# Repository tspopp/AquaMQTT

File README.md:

# AquaMQTT

AquaMQTT is a project designed to monitor and control your DHW heat pump locally using MQTT.

## Features

- Access sensor data and operational states from your heat pump.
- Control the heat pump: Set operational states e.g. water temperature and operation modes.
- [Automate the behavior of your heat pump according to your local energy production or energy availability](/README-PV.md)
- Easily integrate AquaMQTT with smart home systems like [Home Assistant](https://www.home-assistant.io/).

## Compatible Devices

AquaMQTT has been designed and tested with the [Windhager AquaWin Air3](https://www.windhager.com/en/products/hot-water-tanks/aquawin-air3/) DHW heat pump. While specifically tailored to this model, it has been proofen that AquaMQTT is compatible to similar heat pumps manufactured by the [Groupe Atlantic](https://www.groupe-atlantic.fr/) and branded for various companies such as:

- [Atlantic Explorer](https://www.atlantic-comfort.com/Water-Heaters/Heat-pump-water-heaters/Explorer)
- [Atlantic Calypso](https://atlantic-comfort.com/products/domestic-hot-water/heat-pump-water-heaters/calypso-vm)
- [Austria Email Explorer](https://www.austria-email.de/produkte/waermepumpensysteme/waermepumpen-trinkwasser/explorer-evo-2/)
- [Panasonic DHW270](https://www.aircon.panasonic.eu/CH_de/model/paw-dhw270f/)
- [Sauter Confort Pagosa Green](https://www.confort-sauter.com/chauffe-eau/pagosa-green)
- [Thermor Aeromax](https://www.thermor.com/our-solutions/renewable-energy-solutions/heat-pump-water-heaters/aeromax-premium)

A list of community proofen compatible devices is [here](./DEVICES.md).

## How does it work?

AquaMQTT facilitates communication between the HMI controller and the main controller of your heat pump. The project intercepts the serial messages exchanged between these controllers, extracts and parses identified values, and publishes them via [MQTT](./MQTT.md). For a detailed description of the heat pump's serial protocol, refer to [PROTOCOL.md](./PROTOCOL.md).

To achieve this communication interception, an Arduino-based microcontroller is introduced between the communication lines of the HMI controller and the main controller.

AquaMQTT not only monitors the heat pump's status but also provides the capability to control it by modifying the messages originating from the HMI controller. This allows you to set operational states, such as water temperature and operation modes, directly through AquaMQTT.

## Getting Started

- [Hardware Requirements](/pcb) 

- [Software Installation](AquaMQTT/README.md)

- [Heatpump Modification](./WIRING.md)

## Why not using cozytouch / io-homecontrol?

Unfortunately, I had no success pairing those solutions with my Windhager branded heatpump. Moreover, this solution is independent from any manufacturer backends and therefore running entirely within your private local area network. 

## Further Reading

- [HomeAssistant Integration](./HOMEASSISTANT.md)

- [Troubleshooting / F.A.Q](./TROUBLESHOOTING.md)

- [Compatible Devices](./DEVICES.md)
 
- [Heat pump serial protocol (LEGACY)](./PROTOCOL.md)

- [Heat pump serial protocol (NEXT)](./PROTOCOL_NEXT.md)

- [Heat pump serial protocol (ODYSSEE)](./PROTOCOL_ODYSSEE.md)

- [Available MQTT Topics and Payloads](./MQTT.md)

- [Utilize excess local energy using PV modes](./README-PV.md)

## References

- 🇫🇷 https://forum.hacf.fr/t/integration-dun-chauffe-eau-atlantic-explorer-en-mqtt/40493/6
- 🇳🇱 https://gathering.tweakers.net/forum/list_messages/2116816/78
- 🇩🇪 https://forum.iobroker.net/topic/61801/skript-atlantic-w%C3%A4rmepumpe-%C3%BCber-cozytouch-abfragen/74

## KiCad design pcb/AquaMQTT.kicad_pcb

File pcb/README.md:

# AquaMqtt PCB Board

The AquaMQTT PCB Board is intended to be installed between the communication wires of the DHW HMI Controller and the DHW
Mainboard. To enable the communication to both HMI Controller and DHW Mainboard, the board provides two
individual [USART entities in One-Wire Mode](https://ww1.microchip.com/downloads/en/AppNotes/USART-in-One-Wire-Mode-ApplicationNote-DS00002658.pdf).
The Arduino ESP32 on the board runs AquaMQTT, providing communication via WiFi/MQTT while being powerful enough to
handle any time critical USART communication with the heat pumps hmi controller and main board.

The boards are designed using [Kicad](https://www.kicad.org/). If you want to edit the layout, you may need to install an
additional [Arduino Kicad library](https://github.com/Alarm-Siren/arduino-kicad-library) before opening/editing the
project.

## Changelog

| Version | Description                                       |
|---------|---------------------------------------------------|
| 2.0     | RAST Sockets, SMD SN74LVC2T45, Pre-assembly Ready |
| 1.0     | Initial Design, Self-Soldering                    |

## Revision 2.0

***Note*: Revision 2.0 needs AquaMQTT v1.7.0 or later for MITM mode**

This revision fixes an issue, where [certain heatpumps](https://github.com/tspopp/AquaMQTT/issues/67) were not able to communicate due to a very sensitive serial link and changes of impedance. The Logic-Level-Converter and the one-wire USART circuit have been replaced by two [SN74LVC2T45](https://www.ti.com/lit/ds/symlink/sn74lvc2t45.pdf?ts=1740403453841&ref_url=https%253A%252F%252Fwww.ti.com%252Fproduct%252Fde-de%252FSN74LVC2T45). Thanks to [@Arrnooo](https://github.com/Arrnooo) for debugging, verifying and providing a new design proposal.

Additionally, this revision adds optional RAST sockets. Thanks to [@tukutt](https://github.com/tukutt) for providing the design and custom adapters, originally used with revision 1.0 of the AquaMQTT board (see below).

### Buy Pre-Assembled

This board uses tiny SMD SSOP parts (SN74LVC2T45) so self-soldering is most probably an issue. This revision is meant to be bought pre-assembled from [JLCPCB](https://jlcpcb.com/)

1. Upload `AquaMQTT_Board_Revision_v2.zip` as *gerber file*
2. Enable "PCB Assembly"
3. Proceed and upload `AquaMQTT_Board_Revision_v2_BOM.csv` as *BOM*
4. Proceed and upload `AquaMQTT_Board_Revision_v2_CPL.csv` as *CPL*
5. Verify matched parts (should be good out of the box)
6. Verify component placement (should be good out of the box)

If there are any issues during production, [you may reference a successful previous order](https://github.com/tspopp/AquaMQTT/issues/96).

### Parts

| Item                                                                                                                                                                                     | Count | Estimated Cost |
|------------------------------------------------------------------------------------------------------------------------------------------------------------------------------------------|-------|----------------|
| Pre-Soldered AquaMQTT Board (Revision 2.0)  (https://jlcpcb.com/)                                                                                                                        | 1x    | ~ 6 $          |
| [Arduino Nano ESP32](https://docs.arduino.cc/hardware/nano-esp32) with Headers (ABX00083). Note: Community suggested [cheaper alternative](https://github.com/tspopp/AquaMQTT/issues/56) | 1x    | ~ 5-20 €       |

## Revision 1.0

**First revision, which is still good to use. There is no need to replace it with revision 2.0 in case it works for your heatpump.**

An optional DS3231 Real Time Clock might be added to the board. This might be handy in case AquaMQTT will be ever used without any HMI at all. It would ensure a recovery with correct date and time after power outage and without WiFi.
**Adding a RTC Module is experimental and untested!**

### RAST vs. 2x4 Connector

Your [heat pump](./../DEVICES.md) may use a different connector such as the Thermor Aeromax 5. Happily [@tukutt](https://github.com/tukutt) designed an [adapter pcb](https://oshwlab.com/tukutt/aquamqtt-original-pcb-to-rast-co) to connect those heatpumps without cutting any cables. Read more about this in [#51](https://github.com/tspopp/AquaMQTT/issues/51).

### BOM

| Item                                                                                                                                                             | Count | Estimated Cost |
|------------------------------------------------------------------------------------------------------------------------------------------------------------------|-------|----------------|
| AquaMqtt PCB Board (e.g. via AISLER.net)                                                                                                                         | 1x    | ~ 7 €          |
| [Arduino Nano ESP32](https://docs.arduino.cc/hardware/nano-esp32). Note: Community suggested [cheaper alternative](https://github.com/tspopp/AquaMQTT/issues/56) | 1x    | ~ 20 €         |
| Cable 2x4 2,54mm (Socket-Housing, Contacts, Wiring, [Dupont](https://amzn.eu/d/fQyKTWX)                                                                          | 1x    | ~ 10 €         |
| [Real Time Clock RTC DS3231](https://www.az-delivery.de/products/ds3231-real-time-clock) *(optional, experimental)*                                              | (1x)  | ~ 6 €          |
| [SparkFun Logic Level Converter](https://eckstein-shop.de/SparkFunLogicLevelConverter-Bi-DirectionaShifterPegelwandlerEN) - 3.3V to 5V Bi-Directional or similar | 1x    | ~ 4 €          |
| 100k Resistance 0207 (Ø x L) 2.5 mm x 6.8 mm                                                                                                                     | 3x    | < 1 €          |
| 10k Resistance 0207 (Ø x L) 2.5 mm x 6.8 mm                                                                                                                      | 3x    | < 1 €          |
| 4.7k Resistance 0207 (Ø x L) 2.5 mm x 6.8 mm                                                                                                                     | 3x    | < 1 €          |
| [Transistor BC547A TO-92](https://www.conrad.de/de/p/tru-components-transistor-bjt-diskret-tc-bc547a-to-92-anzahl-kanaele-1-npn-1581825.html)                    | 4x    | < 1 €          |
| Pin Header 2x4 2,54mm                                                                                                                                            | 2x    | < 1 €          |
| [Pin Header 1x4 2,54mm](https://www.conrad.de/de/p/mpe-garry-stiftleiste-standard-anzahl-reihen-1-polzahl-je-reihe-4-087-1-004-0-s-xs0-1260-1-st-733940.html)    | 2x    | < 1 €          |
| [Pin Header 1x2 2,54mm](https://www.conrad.de/de/p/mpe-garry-stiftleiste-standard-anzahl-reihen-1-polzahl-je-reihe-2-087-1-002-0-s-xs0-1260-1-st-733900.html)    | 1x    | < 1 €          |

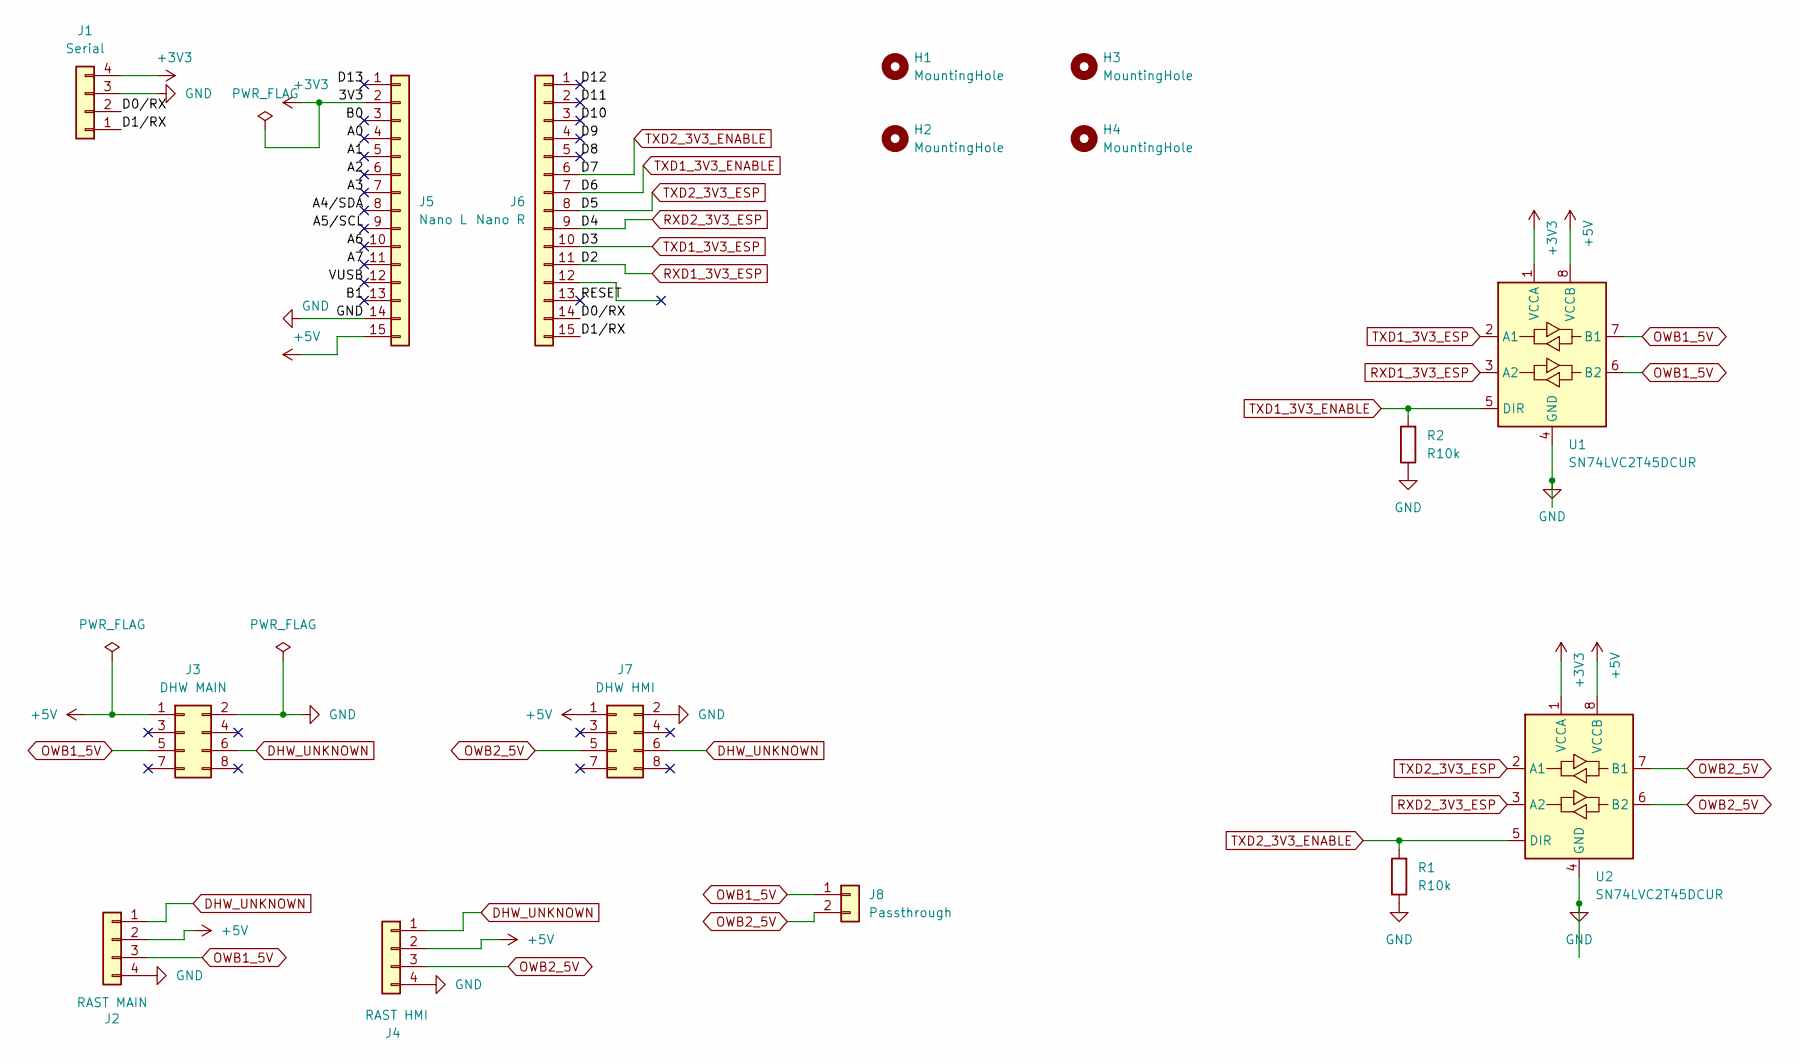
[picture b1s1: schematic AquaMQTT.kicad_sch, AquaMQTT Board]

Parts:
H1, H2, H3, H4: MountingHole; MountingHole_4.3mm_M4_DIN965
J1: Serial; PinHeader_1x04_P2.54mm_Vertical; LCSC C5116483
J2: RAST MAIN; RAST_3517-06_(2.5MM)_2 COPY
J3: DHW MAIN; PinHeader_2x04_P2.54mm_Vertical; LCSC C32713277
J4: RAST HMI; RAST_3517-06_(2.5MM)_2 COPY
J5: Nano L; PinSocket_1x15_P2.54mm_Vertical; LCSC C7499333
J6: Nano R; PinSocket_1x15_P2.54mm_Vertical; LCSC C7499333
J7: DHW HMI; PinHeader_2x04_P2.54mm_Vertical; LCSC C32713277
J8: Passthrough; PinHeader_1x02_P2.54mm_Vertical; LCSC C5360898
R1, R2: R10k; R_Axial_DIN0207_L6.3mm_D2.5mm_P10.16mm_Horizontal; LCSC C410695
U1, U2: SN74LVC2T45DCUR; SSOP-8_2.95x2.8mm_P0.65mm; LCSC C347590

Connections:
+3V3: J1.4, J5.2, U1.1 (VCCA), U2.1 (VCCA)
+5V: J2.2, J3.1, J4.2, J5.15, J7.1, U1.8 (VCCB), U2.8 (VCCB)
/A0: J5.4
/A1: J5.5
/A2: J5.6
/A3: J5.7
/A4/SDA: J5.8
/A5/SCL: J5.9
/A6: J5.10
/A7: J5.11
/B0: J5.3
/B1: J5.13
/D0/RX: J1.2, J6.14
/D1/RX: J1.1, J6.15
/D8: J6.5
/D9: J6.4
/D10: J6.3
/D11: J6.2
/D12: J6.1
/D13: J5.1
/RESET: J6.13
/VUSB: J5.12
DHW_UNKNOWN: J2.1, J3.6, J4.1, J7.6
GND: J1.3, J2.4, J3.2, J4.4, J5.14, J7.2, R1.1, R2.1, U1.4 (GND), U2.4 (GND)
OWB1_5V: J2.3, J3.5, J8.1, U1.6 (B2), U1.7 (B1)
OWB2_5V: J4.3, J7.5, J8.2, U2.6 (B2), U2.7 (B1)
RXD1_3V3_ESP: J6.11, U1.3 (A2)
RXD2_3V3_ESP: J6.9, U2.3 (A2)
TXD1_3V3_ENABLE: J6.7, R2.2, U1.5 (DIR)
TXD1_3V3_ESP: J6.10, U1.2 (A1)
TXD2_3V3_ENABLE: J6.6, R1.2, U2.5 (DIR)
TXD2_3V3_ESP: J6.8, U2.2 (A1)

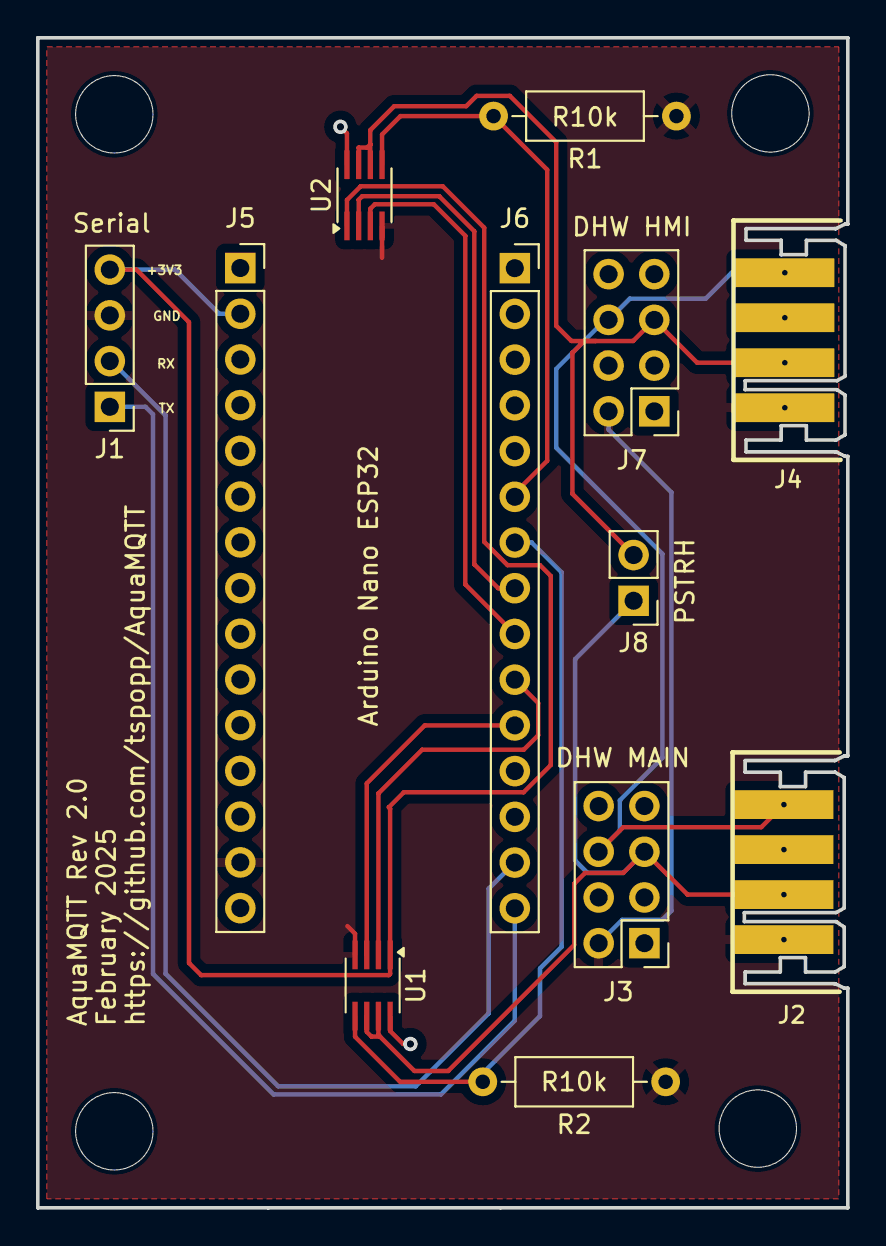
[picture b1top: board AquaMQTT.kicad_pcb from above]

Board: 2 copper layers, 45.0 x 65.0 mm, 16 parts (0 on the bottom side), 14 nets.

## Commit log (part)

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2023-09-08 init(media)
2023-09-08 init(repo): protocol and basic mqtt bridge
2023-09-09 feat(logger): provide operation mode and type
2023-09-10 feat(logger): provide heatpump states
2023-09-10 update(screenshot): homeassistant
2023-09-10 feat(logger): provide heatpump states (#2)
2023-09-10 fix(workflow): working directory
2023-09-10 feat(workflow): add github workflow for platformio build (#3)
2023-11-06 draft(control): building hmi messages, control heatpump
2023-11-06 draft(simulation): simple uno sketch which simulates the main heatpump controller
2023-11-06 doc(Hardware): added section regarding hardware
2023-11-07 feat(prototype): proof controlability of heatpump (#4)
    Added simple sketch which simulates the main controller.
    Added functionality to control the heatpump to AquaMQTTLogger.
    Updated Documentation and Roadmap
    Proof of communication to hmi controller and main controller.
2023-11-13 add(board): added pcb board images
2023-11-13 feat(pcb): initial pcb layout
2023-12-07 docs(README): updated roadmap
2023-12-09 fix(warnings): clang etc..
2023-12-09 init(aquamqtt): basic functionality
2023-12-09 refactor(aquamqtt): various improvements
2023-12-09 doc(readme): updated readme
2023-12-09 refactor(constants): get rid of magic numbers
2023-12-09 feat(mqtt-controlability): prepare more hmi overrides
2023-12-09 fix(reset): reduced ntp timeout which lead to watchdog reset
2023-12-09 refactor(mqtt): refactored mqtt messages
2023-12-09 doc(readme): more nicer readme
2023-12-09 doc(readme): more readme
2023-12-09 fix(build): 2
2023-12-09 feat(aquamqtt): initial version
2023-12-11 fix(temp, installationConfig, watchdog): fixes various issues
2023-12-11 fix(mqtt): fixed mqtt update frequency
2023-12-20 fix(aquamqtt): fixed various issues observed during the initial trial
    Added MQTT Command reset to remove all overrides in MITM mode at once
    Added MQTT Topic activeOverrides which provides a status on all overrriden values in MITM mode
    Fixed Parsing of DHW's Installation Mode
    Fixed Parsing of Float Temperatures (Negative Values e.g. -0.1°C were broken)
    Fixed OTA and Unexpected Reboots due to Watchdog: Increased Watchdog Timer to 60 seconds
    Fixed MQTT Update Cycle: MQTT Topics are now only updated, when a change in the DHW message occur
2023-12-20 doc(wiring): init
2023-12-23 fix(time): fixed invalid date and time values in override mode
2024-01-09 docs(wiring): use media
2024-01-09 fix(suffix): fixed file suffix
2024-01-09 doc(readme): updated images
2024-01-29 fix(connectivity): reconnect to mqtt on lost connection (#10)
2024-02-12 fix(connectivity): proper wifi reconnect
2024-02-23 feat(pv-overrides): use excess energy to reach maximum temperature
2024-02-23 revert(customconfig)
2024-02-23 fix(link)
2024-02-27 feat(pv-overrides): use excess energy to reach maximum temperature (#11)
2024-04-20 doc(mqtt): fix typo in pv heatelement topic
2024-04-20 doc(mqtt): fix typo in pv heatelement topic (#13)
2024-04-23 Add Home Assistant Configuration for AquaMQTT
    English version.
    Change "atlantic_" with your device name.
    Adapt "state_topic:" with your path
2024-04-24 feat(homeassistant): add example homeassistant configuration (#15)
    Add Home Assistant Configuration for AquaMQTT:
    English version.
    Change "atlantic_" with your device name.
    Adapt "state_topic:" with your path
    Thanks to @scoudibou!
2024-05-01 doc(readme): add potential device from sauter confort
2024-05-16 doc(readme): added thermor airomax 5 as proofen device
2024-05-28 doc(mqtt): update mqtt topics
2024-05-28 feat(mitm): transfer errors in mitm mode
2024-05-28 feat(debug): option to publish raw messages
2024-05-28 fix(fan): represent fan speed in percent not rpm
2024-05-28 feat(parsing): parse pv input status and states
2024-05-28 feat(protocol): documented latest protocol findings
2024-05-28 feat(parsing): implemented settings provided from main
2024-05-28 fix(mitm): fixed dropped bytes in main channel
2024-05-28 chore(doc): update latest protocol findings
2024-06-12 doc(readme): added austria email explorer evo 2 as proofen device
2024-06-12 feat(pv-overrides): show solar and pv icons on hmi controller
2024-06-15 refactor(progmem): use constexpr instead of progmem
2024-06-15 revert(ota)
2024-06-15 feat(aquadbg): another troubleshooting tool
2024-06-15 refactor(progmem)
2024-06-15 doc(troubleshooting): add section regarding AquaDebug
2024-06-15 feat(aquadbg): more troubleshooting tooling (#27)
2024-08-17 adapted documentation to new attribute
2024-08-17 revert platformio ota
2024-08-19 chore(renaming): renamed from water consumption to production
2024-08-19 homeassistant
2024-08-19 fix(wifi): do not trust platform auto reconnect routines (#32)
2024-09-11 refactor(framebuffer): remove dead code left from debugging session
    - fixes #34
2024-09-13 feat(framework): upgrade to arduino core 3.0.4 / esp-idf v5.1.4 via pioarduino
    - fixes #35
2024-09-14 revert(framework): back to v4 framework due to broken ota and ntp
2024-10-13 feat(filter): filter temperature values published to mqtt using kalman filter
2024-10-13 fix(aquamqtt): fix broken ntp update
2024-10-14 feat(mqtt): filter temperature values using kalman (#38)
2024-10-19 chore(various): enable unittests in ci, pin library versions, adapt watchdog, remove magic numbers
2024-10-20 feat(homeassistant): enable homeassistant discovery
    refactor(mqtt): use arduino json for overrides
    doc(homeassistant): some remarks to homeassistant integration
    refactor(discovery): various items from test
2024-10-24 feat(fan): allow controlability of airduct and exhaust fan configuration
2024-10-24 chore(version): increase version
2024-10-24 feat(fan): allow controlability of airduct and exhaust fan configuration (#44)
2024-10-29 Add water_heater integration
    https://www.home-assistant.io/integrations/water_heater.mqtt/
2024-11-01 feat(mqtt): more options to disable frequent changing topics
2024-11-01 feat(homeassisant): add water heater integration to auto discovery
2024-11-02 Add .vscode folder to gitignore
2024-11-02 Added option for uploading with Esptool in Platformio
2024-11-03 chore(homeassistant): add water_heater to homeassistant template
2024-11-03 chore(homeassistant): add water_heater to homeassistant template
    * Add water_heater integration
    https://www.home-assistant.io/integrations/water_heater.mqtt/
    * chore(homeassistant): add water_heater to homeassistant template
    ---------
2024-11-03 feat(mqtt): configuration options to disable several debugging mqtt topics (#48)
    * feat(mqtt): more options to disable frequent changing topics
    * config: set serial statistics to on by default
2024-11-03 wip(protocol-next): first steps
2024-11-04 wip(protocol): doc, fixed date, add water temp target, add operation type and modes
2024-11-05 wip(protocol): pv status
2024-11-09 wip(protocol): prepare to support both protocols in parallel
2024-11-09 wip(protocol): parse timers
2024-11-09 wip(protocol): power heatpump, total energy, total energy heatpump
2024-11-10 doc(devices): rast adapter, list of devices with sw version
2024-11-11 doc(devices): rast adapter, list of devices with sw version (#54)
2024-11-11 wip(protocol): identified error messages
2024-11-12 wip(protocol): proper checksum calcuation and generation, parse errors, enable mitm (experimental)
2024-11-15 Update PROTOCOL_NEXT.md
    Texts corrected
    To-dos completed
    Unassigned values added
2024-11-20 refactor(protocols): support multiple protocols
2024-11-20 wip(protocol): main states, pwm fan speed
2024-11-25 fix(build): disable custom configuration for pipeline to success
2024-11-25 hack(watchdog): intermediate fix for reboot issue
2024-11-26 experimental(next): allow overrides in mitm mode
2024-11-26 doc(mqtt): fix table
2024-11-26 feat(protocol-next): initial support for additional heatpump protocol E/E
2024-12-04 feat(protocol-next): full support of E/E protocol (next)
2025-01-19 Update framework and wifi handler
2025-01-19 feat(aquadebug): build aquadebug in ci/cd, pin versions
2025-01-19 feat(aquadebug): build aquadebug in ci/cd, pin versions (#61)
2025-01-19 feat(platformio): add environment for esp32-s3-devkitc-1
2025-01-19 feat(platformio): add environment for esp32-s3-devkitc-1 (#62)
2025-01-19 feat(aquamqtt): support legacy protocol with XOR checksum
2025-01-19 build(esp32-devkit): apply suggestions from community
2025-02-03 add tx enable gpio for hmi and controller channel
2025-02-10 prepare(protocol-odyssee): preparation for another heat-pump protocol
2025-02-11 Update configuration to reduce amount of MQTT messages by default
    This resolves issues with specificly new users that are getting unexpected results due to a flood of update messages.
2025-02-11 chore(mqtt): disable debug and time/date topics in default configuration
    This resolves issues with specificly new users that are getting unexpected results due to a flood of update messages.
2025-02-11 doc(mqtt): add note how to enable serial debug options
2025-02-14 wip(odyssee): parse operation mode accordingly
2025-02-15 fix(odyssee): provide time and date
2025-02-15 feat(odyssee): add totalPower and grid voltage from message 217
2025-02-15 feat(debug): possibility to debug frame timing intervalls
2025-03-02 addMqttConfigHandling
2025-03-09 remove html file
2025-03-27 feat(pcb): added pcb in rev 2.0 (rast, pre-assembly, sn74lvct45)
2025-03-27 doc(hw): added note regarding 1.7.0
2025-03-27 feat(odyssee): support heat-pump protocol odyssee
2025-03-27 feat(odyssee): implemented more odyssee attributes
2025-03-27 feat(odyssee): added overrides, enabled pv mode
2025-03-27 fix(hw): fix dropped bytes in hmi channel with rev2.0 board
2025-03-27 chore(config): back to default values
2025-03-30 doc(readme): added discord for community and pcb trading possibility
2025-03-30 doc(readme): fix discord link
2025-03-31 Fix PR comments
2025-04-09 chore(version): bump version to v1.7.1
2025-04-09 fix(next): fix option allow heat element and pv mode heat element (#75)
    * fix(next): fix heating element enabled switch
    * chore(version): bump version to v1.7.1
2025-04-14 fix(next): fix parsing of operation type (#78)
2025-04-15 Fix settingBoilerBrand output
2025-04-16 fix(aquamqtt): provide proper boiler brand to mqtt (#79)
2025-04-23 chore(version): bump to v1.7.2
2025-04-23 test(protocol): unittest for hmi protocol overrides (next/legacy/odyssee)
2025-04-23 fix(next/odyssee): proper date overrides
2025-05-05 feat(protocol): parse and provide software version attributes
2025-05-22 increased buffer for debugging
2025-08-03 fix(serial): allow serial configuration from configuration file
2025-08-03 fix(serial): allow serial configuration from configuration file (#88)
2025-08-06 added a guide inside of HOMEASSISTANT.md` to setup a climat entity
2025-08-08 Updated HOMEASSISTANT.md with 3 showcase images from ./img
2025-08-09 doc(homeassistant): added guide to setup climate entity (#89)
    * added a guide inside of HOMEASSISTANT.md` to setup a climat entity
    * added custom climate card showcase images
    * Updated HOMEASSISTANT.md with 3 showcase images from ./img
2025-08-09 prototype(cv5): dumping isolated modbus messages to mqtt
2025-11-08 fix(mitm): fix issue where invalid time overrides caused inoperative heatpumps
    The mLastStateUpdate variable was declared as time_t (signed integer)
    while being compared with millis() return values (unsigned long). This
    caused incorrect behavior after millis() exceeded the maximum signed
    integer value (2,147,483,647ms / ~24.8 days), causing time updates to
    stop being sent.
    Changed mLastStateUpdate to unsigned long to match the type returned by
2025-11-08 chore(release): bump version to v1.8.0
2025-11-08 feat(climate): add climate component to home-assistant discovery
2025-11-09 prepare(legacy_alt): prepare support of alternative legacy protocol
2025-11-13 feat(climate): add climate component to home-assistant discovery (#100)
2025-11-25 feat(alt): no evaporator lower
2025-11-25 feat(alt): fix evaporator air temp
2025-11-25 feat(alt): no fan speed pwm
2025-11-25 feat(alt): remove settings
2025-12-22 Update HomeAssistant integration for AquaMQTT
2026-01-17 #111 Link additional cable in documentation
2026-01-18 doc(pcb): add suggestion for dupont cables (#114)
2026-01-18 doc(devices): updated list of devices
2026-05-03 add requirements.txt (#121)
